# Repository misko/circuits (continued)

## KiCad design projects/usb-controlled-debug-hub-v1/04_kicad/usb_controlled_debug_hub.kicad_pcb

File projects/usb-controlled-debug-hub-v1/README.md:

# USB controlled debug hub v1

Four-port self-powered USB 2.0 debug hub with independent per-port VBUS and
D+/D- control through an onboard USB management function.

Status: commission and exact-part sourcing in progress. No release exists and
the board is not ready to order.

Firmware is outside scope. See `01_docs/BRIEF.md` for the commission and
`01_docs/ARCHITECTURE.md` for the locked topology.

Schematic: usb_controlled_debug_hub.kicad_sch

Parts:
C_AGG_DVDT: 3.3nF; C_0603_1608Metric
C_AGG_IN: 100nF; C_0402_1005Metric
C_AGG_TIMER: 3.3nF; C_0603_1608Metric
C_AND_DATA: 100nF; C_0402_1005Metric
C_AND_PWR: 100nF; C_0402_1005Metric
C_BST: 100nF; C_0402_1005Metric
C_BUCK_IN: 10uF; C_0603_1608Metric
C_BUCK_OUT1, C_BUCK_OUT2: 22uF; C_1210_3225Metric
C_CTRL_VDD: 100nF; C_0402_1005Metric
C_CTRL_VUSB: 330nF; C_0402_1005Metric
C_DATA1, C_DATA2, C_DATA3, C_DATA4: 100nF; C_0402_1005Metric
C_EXP_VDD: 100nF; C_0402_1005Metric
C_HUB_18, C_HUB_18PLL: 1uF; C_0402_1005Metric
C_HUB_A1, C_HUB_A2, C_HUB_A3, C_HUB_A4: 100nF; C_0402_1005Metric
C_HUB_A_BULK: 1uF; C_0402_1005Metric
C_HUB_CR_BULK: 1uF; C_0402_1005Metric
C_HUB_CR_HF: 100nF; C_0402_1005Metric
C_HUB_DD: 100nF; C_0402_1005Metric
C_HUB_PLL: 100nF; C_0402_1005Metric
C_HUB_RESET: 1uF; C_0402_1005Metric
C_PORT1_BULK, C_PORT2_BULK, C_PORT3_BULK, C_PORT4_BULK: 22uF; C_1210_3225Metric
C_PORT1_HF, C_PORT2_HF, C_PORT3_HF, C_PORT4_HF: 100nF; C_0402_1005Metric
C_PWR1_IN, C_PWR2_IN, C_PWR3_IN, C_PWR4_IN: 100nF; C_0402_1005Metric
C_PWR_CTRL_IN: 100nF; C_0402_1005Metric
C_PWR_CTRL_OUT: 1uF; C_0402_1005Metric
C_PWR_CTRL_OUT_HF: 100nF; C_0402_1005Metric
C_TRUNK_BULK: 22uF; C_1210_3225Metric
C_TRUNK_HF: 100nF; C_0402_1005Metric
C_TRUNK_USB: 180uF; CP_Elec_6.3x5.8
C_XTAL1, C_XTAL2: 18pF; C_0402_1005Metric
F_IN: 3568; Fuseholder_Blade_Mini_Keystone_3568
J_PORT1, J_PORT2, J_PORT3, J_PORT4: C503996; KH-AF90DIP-112_Horizontal
J_PWR: C3819953; Phoenix_1935161_PT_1p5_2_5p0_H
J_UP: C86462; USB_B_TE_292304-1_Horizontal
L_MAIN: C15269; Sunlord_SWPA4030S
Q_DATA1, Q_DATA2, Q_DATA3, Q_DATA4: C85047; Diodes_SOT23_2N7002K
R_AGG_ILIM: 1kΩ; R_0603_1608Metric
R_AGG_OV_BOT: 43.2kΩ; R_0603_1608Metric
R_AGG_UV_MID: 10kΩ; R_0603_1608Metric
R_AGG_UV_TOP: 150kΩ; R_0603_1608Metric
R_BOOST0, R_BOOST1: 10kΩ; R_0402_1005Metric
R_CFG0, R_CFG1, R_CFG2: 10kΩ; R_0402_1005Metric
R_CTRL_RESET: 10kΩ; R_0402_1005Metric
R_DATA_CMD1, R_DATA_CMD2, R_DATA_CMD3, R_DATA_CMD4: 10kΩ; R_0402_1005Metric
R_DATA_OE1, R_DATA_OE2, R_DATA_OE3, R_DATA_OE4: 10kΩ; R_0402_1005Metric
R_DATA_OK1, R_DATA_OK2, R_DATA_OK3, R_DATA_OK4: 10kΩ; R_0402_1005Metric
R_DIS6N, R_DIS6P, R_DIS7N, R_DIS7P: 10kΩ; R_0402_1005Metric
R_EXP_RESET: 10kΩ; R_0402_1005Metric
R_GANG: 10kΩ; R_0402_1005Metric
R_HUB_RESET: 10kΩ; R_0402_1005Metric
R_I2C_SCL, R_I2C_SDA: 4.7kΩ; R_0402_1005Metric
R_ILIM1, R_ILIM2, R_ILIM3, R_ILIM4: 165kΩ; R_0402_1005Metric
R_ILIM_CTRL: 165kΩ; R_0402_1005Metric
R_NONREM0, R_NONREM1: 10kΩ; R_0402_1005Metric
R_PWR_CMD1, R_PWR_CMD2, R_PWR_CMD3, R_PWR_CMD4: 10kΩ; R_0402_1005Metric
R_PWR_EN1, R_PWR_EN2, R_PWR_EN3, R_PWR_EN4: 10kΩ; R_0402_1005Metric
R_RBIAS: 12kΩ; R_0402_1005Metric
R_SWAP1, R_SWAP2, R_SWAP3, R_SWAP4, R_SWAP5, R_SWAP6, R_SWAP7: 100kΩ; R_0402_1005Metric
R_VBUS_BOT: 100kΩ; R_0402_1005Metric
R_VBUS_TOP: 100kΩ; R_0402_1005Metric
R_XTAL: 1MΩ; R_0402_1005Metric
U_AGG: C2864845; TI_RPW0010A_VQFN-HR-10_2x2mm_P0.45mm
U_AND_DATA: C6053; TSSOP-14_4.4x5mm_P0.65mm
U_AND_PWR: C6053; TSSOP-14_4.4x5mm_P0.65mm
U_BUCK: C5248536; TSOT-23-6
U_CTRL: C640876; SOIC-14_3.9x8.7mm_P1.27mm
U_DATA1, U_DATA2, U_DATA3, U_DATA4: C11355; MSOP-10_3x3mm_P0.5mm
U_ESD1, U_ESD2, U_ESD3, U_ESD4: C3708426; SOT-23
U_ESD_UP: C3708426; SOT-23
U_EXP: C558584; SSOP-28_5.3x10.2mm_P0.65mm
U_HUB: C478081; QFN-64-1EP_9x9mm_P0.5mm_EP4.7x4.7mm_ThermalVias
U_PWR1, U_PWR2, U_PWR3, U_PWR4: C130056; VSON-8-1EP_3x3mm_P0.65mm_EP1.65x2.4mm_ThermalVias
U_PWR_CTRL: C130056; VSON-8-1EP_3x3mm_P0.65mm_EP1.65x2.4mm_ThermalVias
Y_HUB: C1985204; Crystal_SMD_3225-4Pin_3.2x2.5mm

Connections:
3V3_MAIN: C_AND_DATA.1, C_AND_PWR.1, C_BUCK_OUT1.1, C_BUCK_OUT2.1, C_DATA1.1, C_DATA2.1, C_DATA3.1, C_DATA4.1, C_HUB_A1.1, C_HUB_A2.1, C_HUB_A3.1, C_HUB_A4.1, C_HUB_A_BULK.1, C_HUB_CR_BULK.1, C_HUB_CR_HF.1, C_HUB_DD.1, C_HUB_PLL.1, L_MAIN.2, R_DATA_OE1.1, R_DATA_OE2.1, R_DATA_OE3.1, R_DATA_OE4.1, R_DIS6N.1, R_DIS6P.1, R_DIS7N.1, R_DIS7P.1, R_HUB_RESET.1, R_NONREM0.1, R_SWAP1.2, U_AND_DATA.14 (VCC), U_AND_PWR.14 (VCC), U_BUCK.1 (FB), U_DATA1.1 (VCC), U_DATA2.1 (VCC), U_DATA3.1 (VCC), U_DATA4.1 (VCC), U_HUB.5 (VDDA33_1), U_HUB.10 (VDDA33_2), U_HUB.24 (VDD33CR), U_HUB.46 (VDD33), U_HUB.52 (VDDA33_3), U_HUB.57 (VDDA33_4), U_HUB.64 (VDD33PLL)
AGG_DVDT: C_AGG_DVDT.1, U_AGG.7 (DVDT)
AGG_ILIM: R_AGG_ILIM.1, U_AGG.9 (ILM)
AGG_OV: R_AGG_OV_BOT.1, R_AGG_UV_MID.2, U_AGG.2 (OVLO)
AGG_TIMER: C_AGG_TIMER.1, U_AGG.10 (ITIMER)
AGG_UV: R_AGG_UV_MID.1, R_AGG_UV_TOP.2, U_AGG.1 (EN_UVLO)
BST_3V3: C_BST.1, U_BUCK.6 (BST)
CTRL_RESET_N: R_CTRL_RESET.2, U_CTRL.4 (RST)
CTRL_VUSB_3V3: C_CTRL_VUSB.1, U_CTRL.11 (VUSB)
DATA_CMD1: R_DATA_CMD1.1, U_AND_DATA.2 (1B), U_EXP.25 (GPA4)
DATA_CMD2: R_DATA_CMD2.1, U_AND_DATA.5 (2B), U_EXP.26 (GPA5)
DATA_CMD3: R_DATA_CMD3.1, U_AND_DATA.10 (3B), U_EXP.27 (GPA6)
DATA_CMD4: R_DATA_CMD4.1, U_AND_DATA.13 (4B), U_EXP.28 (GPA7)
DATA_OE1_N: Q_DATA1.3 (D), R_DATA_OE1.2, U_DATA1.10 (OE)
DATA_OE2_N: Q_DATA2.3 (D), R_DATA_OE2.2, U_DATA2.10 (OE)
DATA_OE3_N: Q_DATA3.3 (D), R_DATA_OE3.2, U_DATA3.10 (OE)
DATA_OE4_N: Q_DATA4.3 (D), R_DATA_OE4.2, U_DATA4.10 (OE)
DATA_OK1: Q_DATA1.1 (G), R_DATA_OK1.1, U_AND_DATA.3 (1Y)
DATA_OK2: Q_DATA2.1 (G), R_DATA_OK2.1, U_AND_DATA.6 (2Y)
DATA_OK3: Q_DATA3.1 (G), R_DATA_OK3.1, U_AND_DATA.8 (3Y)
DATA_OK4: Q_DATA4.1 (G), R_DATA_OK4.1, U_AND_DATA.11 (4Y)
EXP_RESET_N: R_EXP_RESET.2, U_EXP.18 (RESET_N)
GND: C_AGG_DVDT.2, C_AGG_IN.2, C_AGG_TIMER.2, C_AND_DATA.2, C_AND_PWR.2, C_BUCK_IN.2, C_BUCK_OUT1.2, C_BUCK_OUT2.2, C_CTRL_VDD.2, C_CTRL_VUSB.2, C_DATA1.2, C_DATA2.2, C_DATA3.2, C_DATA4.2, C_EXP_VDD.2, C_HUB_18.2, C_HUB_18PLL.2, C_HUB_A1.2, C_HUB_A2.2, C_HUB_A3.2, C_HUB_A4.2, C_HUB_A_BULK.2, C_HUB_CR_BULK.2, C_HUB_CR_HF.2, C_HUB_DD.2, C_HUB_PLL.2, C_HUB_RESET.2, C_PORT1_BULK.2, C_PORT1_HF.2, C_PORT2_BULK.2, C_PORT2_HF.2, C_PORT3_BULK.2, C_PORT3_HF.2, C_PORT4_BULK.2, C_PORT4_HF.2, C_PWR1_IN.2, C_PWR2_IN.2, C_PWR3_IN.2, C_PWR4_IN.2, C_PWR_CTRL_IN.2, C_PWR_CTRL_OUT.2, C_PWR_CTRL_OUT_HF.2, C_TRUNK_BULK.2, C_TRUNK_HF.2, C_TRUNK_USB.2, C_XTAL1.2, C_XTAL2.2, J_PORT1.4 (GND), J_PORT1.5 (SHIELD), J_PORT2.4 (GND), J_PORT2.5 (SHIELD), J_PORT3.4 (GND), J_PORT3.5 (SHIELD), J_PORT4.4 (GND), J_PORT4.5 (SHIELD), J_PWR.2 (GND), J_UP.4 (GND), J_UP.5 (SHIELD), Q_DATA1.2 (S), Q_DATA2.2 (S), Q_DATA3.2 (S), Q_DATA4.2 (S), R_AGG_ILIM.2, R_AGG_OV_BOT.2, R_BOOST0.2, R_BOOST1.2, R_CFG0.2, R_CFG1.2, R_CFG2.2, R_DATA_CMD1.2, R_DATA_CMD2.2, R_DATA_CMD3.2, R_DATA_CMD4.2, R_DATA_OK1.2, R_DATA_OK2.2, R_DATA_OK3.2, R_DATA_OK4.2, R_GANG.2, R_ILIM1.2, R_ILIM2.2, R_ILIM3.2, R_ILIM4.2, R_ILIM_CTRL.2, R_NONREM1.2, R_PWR_CMD1.2, R_PWR_CMD2.2, R_PWR_CMD3.2, R_PWR_CMD4.2, R_PWR_EN1.2, R_PWR_EN2.2, R_PWR_EN3.2, R_PWR_EN4.2, R_RBIAS.2, R_SWAP2.2, R_SWAP3.2, R_SWAP4.2, R_SWAP5.2, R_SWAP6.2, R_SWAP7.2, R_VBUS_BOT.2, U_AGG.4 (PGTH), U_AGG.8 (GND), U_AND_DATA.7 (GND), U_AND_PWR.7 (GND), U_BUCK.4 (GND), U_CTRL.14 (VSS), U_DATA1.2 (SEL), U_DATA1.5 (GND), U_DATA2.2 (SEL), U_DATA2.5 (GND), U_DATA3.2 (SEL), U_DATA3.5 (GND), U_DATA4.2 (SEL), U_DATA4.5 (GND), U_ESD1.3 (GND), U_ESD2.3 (GND), U_ESD3.3 (GND), U_ESD4.3 (GND), U_ESD_UP.3 (GND), U_EXP.10 (VSS), U_EXP.15 (A0), U_EXP.16 (A1), U_EXP.17 (A2), U_HUB.65 (EP_VSS), U_PWR1.1 (GND), U_PWR1.9 (EP), U_PWR2.1 (GND), U_PWR2.9 (EP), U_PWR3.1 (GND), U_PWR3.9 (EP), U_PWR4.1 (GND), U_PWR4.9 (EP), U_PWR_CTRL.1 (GND), U_PWR_CTRL.9 (EP), Y_HUB.2 (GND1), Y_HUB.4 (GND2)
HUB_BOOST0: R_BOOST0.1, U_HUB.50 (BOOST0)
HUB_BOOST1: R_BOOST1.1, U_HUB.48 (BOOST1)
HUB_CFG0: R_CFG0.1, U_HUB.41 (CFG_SEL0)
HUB_CFG1: R_CFG1.1, U_HUB.42 (CFG_SEL1)
HUB_CFG2: R_CFG2.1, U_HUB.13 (CFG_SEL2)
HUB_DIS6_N: R_DIS6N.2, U_HUB.53 (DN6_DM)
HUB_DIS6_P: R_DIS6P.2, U_HUB.54 (DN6_DP)
HUB_DIS7_N: R_DIS7N.2, U_HUB.55 (DN7_DM)
HUB_DIS7_P: R_DIS7P.2, U_HUB.56 (DN7_DP)
HUB_GANG: R_GANG.1, U_HUB.34 (GANG_EN)
HUB_NONREM0: R_NONREM0.2, U_HUB.45 (NON_REM0)
HUB_NONREM1: R_NONREM1.1, U_HUB.40 (NON_REM1)
HUB_OCS1_N: U_HUB.28 (OCS1_N), U_PWR_CTRL.8 (FAULT_N)
HUB_OCS2_N: U_HUB.27 (OCS2_N), U_PWR1.8 (FAULT_N)
HUB_OCS3_N: U_HUB.22 (OCS3_N), U_PWR2.8 (FAULT_N)
HUB_OCS4_N: U_HUB.21 (OCS4_N), U_PWR3.8 (FAULT_N)
HUB_OCS5_N: U_HUB.35 (OCS5_N), U_PWR4.8 (FAULT_N)
HUB_PRTPWR1: U_HUB.29 (PRTPWR1), U_PWR_CTRL.4 (EN)
HUB_PRTPWR2: U_AND_PWR.1 (1A), U_HUB.26 (PRTPWR2)
HUB_PRTPWR3: U_AND_PWR.4 (2A), U_HUB.23 (PRTPWR3)
HUB_PRTPWR4: U_AND_PWR.9 (3A), U_HUB.20 (PRTPWR4)
HUB_PRTPWR5: U_AND_PWR.12 (4A), U_HUB.30 (PRTPWR5)
HUB_RESET_N: C_HUB_RESET.1, R_HUB_RESET.2, U_HUB.43 (RESET_N)
HUB_SWAP1: R_SWAP1.1, U_HUB.51 (PRT_SWP1)
HUB_SWAP2: R_SWAP2.1, U_HUB.49 (PRT_SWP2)
HUB_SWAP3: R_SWAP3.1, U_HUB.47 (PRT_SWP3)
HUB_SWAP4: R_SWAP4.1, U_HUB.33 (PRT_SWP4)
HUB_SWAP5: R_SWAP5.1, U_HUB.31 (PRT_SWP5)
HUB_SWAP6: R_SWAP6.1, U_HUB.17 (PRT_SWP6)
HUB_SWAP7: R_SWAP7.1, U_HUB.15 (PRT_SWP7)
HUB_VBUS_SENSE: R_VBUS_BOT.1, R_VBUS_TOP.2, U_HUB.44 (VBUS_DET)
HUB_VDD18: C_HUB_18.1, U_HUB.25 (VDD18)
HUB_VDD18PLL: C_HUB_18PLL.1, U_HUB.62 (VDD18PLL)
I2C_SCL: R_I2C_SCL.2, U_CTRL.10 (SCL), U_EXP.12 (SCL)
I2C_SDA: R_I2C_SDA.2, U_CTRL.9 (SDA), U_EXP.13 (SDA)
ILIM1: R_ILIM1.1, U_PWR1.5 (ILIM)
ILIM2: R_ILIM2.1, U_PWR2.5 (ILIM)
ILIM3: R_ILIM3.1, U_PWR3.5 (ILIM)
ILIM4: R_ILIM4.1, U_PWR4.5 (ILIM)
ILIM_CTRL: R_ILIM_CTRL.1, U_PWR_CTRL.5 (ILIM)
MGMT_N: U_CTRL.12 (D_MINUS), U_HUB.2 (DN1_DP)
MGMT_P: U_CTRL.13 (D_PLUS), U_HUB.1 (DN1_DM)
P1_HUB_N: U_DATA1.3 (D_PLUS), U_HUB.3 (DN2_DM)
P1_HUB_P: U_DATA1.4 (D_MINUS), U_HUB.4 (DN2_DP)
P1_PORT_N: J_PORT1.2 (D_MINUS), U_DATA1.7 (HSD1_PLUS), U_ESD1.2 (IO2)
P1_PORT_P: J_PORT1.3 (D_PLUS), U_DATA1.6 (HSD1_MINUS), U_ESD1.1 (IO1)
P2_HUB_N: U_DATA2.3 (D_PLUS), U_HUB.6 (DN3_DM)
P2_HUB_P: U_DATA2.4 (D_MINUS), U_HUB.7 (DN3_DP)
P2_PORT_N: J_PORT2.2 (D_MINUS), U_DATA2.7 (HSD1_PLUS), U_ESD2.2 (IO2)
P2_PORT_P: J_PORT2.3 (D_PLUS), U_DATA2.6 (HSD1_MINUS), U_ESD2.1 (IO1)
P3_HUB_N: U_DATA3.3 (D_PLUS), U_HUB.8 (DN4_DM)
P3_HUB_P: U_DATA3.4 (D_MINUS), U_HUB.9 (DN4_DP)
P3_PORT_N: J_PORT3.2 (D_MINUS), U_DATA3.7 (HSD1_PLUS), U_ESD3.2 (IO2)
P3_PORT_P: J_PORT3.3 (D_PLUS), U_DATA3.6 (HSD1_MINUS), U_ESD3.1 (IO1)
P4_HUB_N: U_DATA4.3 (D_PLUS), U_HUB.11 (DN5_DM)
P4_HUB_P: U_DATA4.4 (D_MINUS), U_HUB.12 (DN5_DP)
P4_PORT_N: J_PORT4.2 (D_MINUS), U_DATA4.7 (HSD1_PLUS), U_ESD4.2 (IO2)
P4_PORT_P: J_PORT4.3 (D_PLUS), U_DATA4.6 (HSD1_MINUS), U_ESD4.1 (IO1)
P5V_FUSED: C_AGG_IN.1, F_IN.2 (FUSE_OUT), R_AGG_UV_TOP.1, U_AGG.5 (IN)
P5V_PROTECTED: C_BUCK_IN.1, C_PWR1_IN.1, C_PWR2_IN.1, C_PWR3_IN.1, C_PWR4_IN.1, C_PWR_CTRL_IN.1, C_TRUNK_BULK.1, C_TRUNK_HF.1, C_TRUNK_USB.1, U_AGG.6 (OUT), U_BUCK.2 (EN), U_BUCK.3 (VIN), U_PWR1.2 (IN1), U_PWR1.3 (IN2), U_PWR2.2 (IN1), U_PWR2.3 (IN2), U_PWR3.2 (IN1), U_PWR3.3 (IN2), U_PWR4.2 (IN1), U_PWR4.3 (IN2), U_PWR_CTRL.2 (IN1), U_PWR_CTRL.3 (IN2)
P5V_RAW: F_IN.1 (FUSE_IN), J_PWR.1 (P5V_RAW)
PWR_CMD1: R_PWR_CMD1.1, U_AND_PWR.2 (1B), U_EXP.21 (GPA0)
PWR_CMD2: R_PWR_CMD2.1, U_AND_PWR.5 (2B), U_EXP.22 (GPA1)
PWR_CMD3: R_PWR_CMD3.1, U_AND_PWR.10 (3B), U_EXP.23 (GPA2)
PWR_CMD4: R_PWR_CMD4.1, U_AND_PWR.13 (4B), U_EXP.24 (GPA3)
PWR_EN1: R_PWR_EN1.1, U_AND_DATA.1 (1A), U_AND_PWR.3 (1Y), U_PWR1.4 (EN)
PWR_EN2: R_PWR_EN2.1, U_AND_DATA.4 (2A), U_AND_PWR.6 (2Y), U_PWR2.4 (EN)
PWR_EN3: R_PWR_EN3.1, U_AND_DATA.9 (3A), U_AND_PWR.8 (3Y), U_PWR3.4 (EN)
PWR_EN4: R_PWR_EN4.1, U_AND_DATA.12 (4A), U_AND_PWR.11 (4Y), U_PWR4.4 (EN)
RBIAS: R_RBIAS.1, U_HUB.63 (RBIAS)
SW_3V3: C_BST.2, L_MAIN.1, U_BUCK.5 (SW)
UP_HUB_N: J_UP.2 (D_MINUS), U_ESD_UP.1 (IO1), U_HUB.58 (UP_DM)
UP_HUB_P: J_UP.3 (D_PLUS), U_ESD_UP.2 (IO2), U_HUB.59 (UP_DP)
USB_UP_VBUS: J_UP.1 (VBUS), R_VBUS_TOP.1
VBUS1_SW: C_PORT1_BULK.1, C_PORT1_HF.1, J_PORT1.1 (VBUS), U_PWR1.6 (OUT1), U_PWR1.7 (OUT2)
VBUS2_SW: C_PORT2_BULK.1, C_PORT2_HF.1, J_PORT2.1 (VBUS), U_PWR2.6 (OUT1), U_PWR2.7 (OUT2)
VBUS3_SW: C_PORT3_BULK.1, C_PORT3_HF.1, J_PORT3.1 (VBUS), U_PWR3.6 (OUT1), U_PWR3.7 (OUT2)
VBUS4_SW: C_PORT4_BULK.1, C_PORT4_HF.1, J_PORT4.1 (VBUS), U_PWR4.6 (OUT1), U_PWR4.7 (OUT2)
VBUS_CTRL: C_CTRL_VDD.1, C_EXP_VDD.1, C_PWR_CTRL_OUT.1, C_PWR_CTRL_OUT_HF.1, R_CTRL_RESET.1, R_EXP_RESET.1, R_I2C_SCL.1, R_I2C_SDA.1, U_CTRL.1 (VDD), U_EXP.9 (VDD), U_PWR_CTRL.6 (OUT1), U_PWR_CTRL.7 (OUT2)
XTAL1: C_XTAL1.1, R_XTAL.1, U_HUB.61 (XTAL1), Y_HUB.1 (X1)
XTAL2: C_XTAL2.1, R_XTAL.2, U_HUB.60 (XTAL2), Y_HUB.3 (X2)

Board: 4 copper layers, 146 parts (9 on the bottom side), 104 nets, no tracks yet.

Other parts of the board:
FID1, FID2, FID3: Fiducial_1mm_Mask2mm
H1, H2, H3, H4: MountingHole_3.2mm_M3

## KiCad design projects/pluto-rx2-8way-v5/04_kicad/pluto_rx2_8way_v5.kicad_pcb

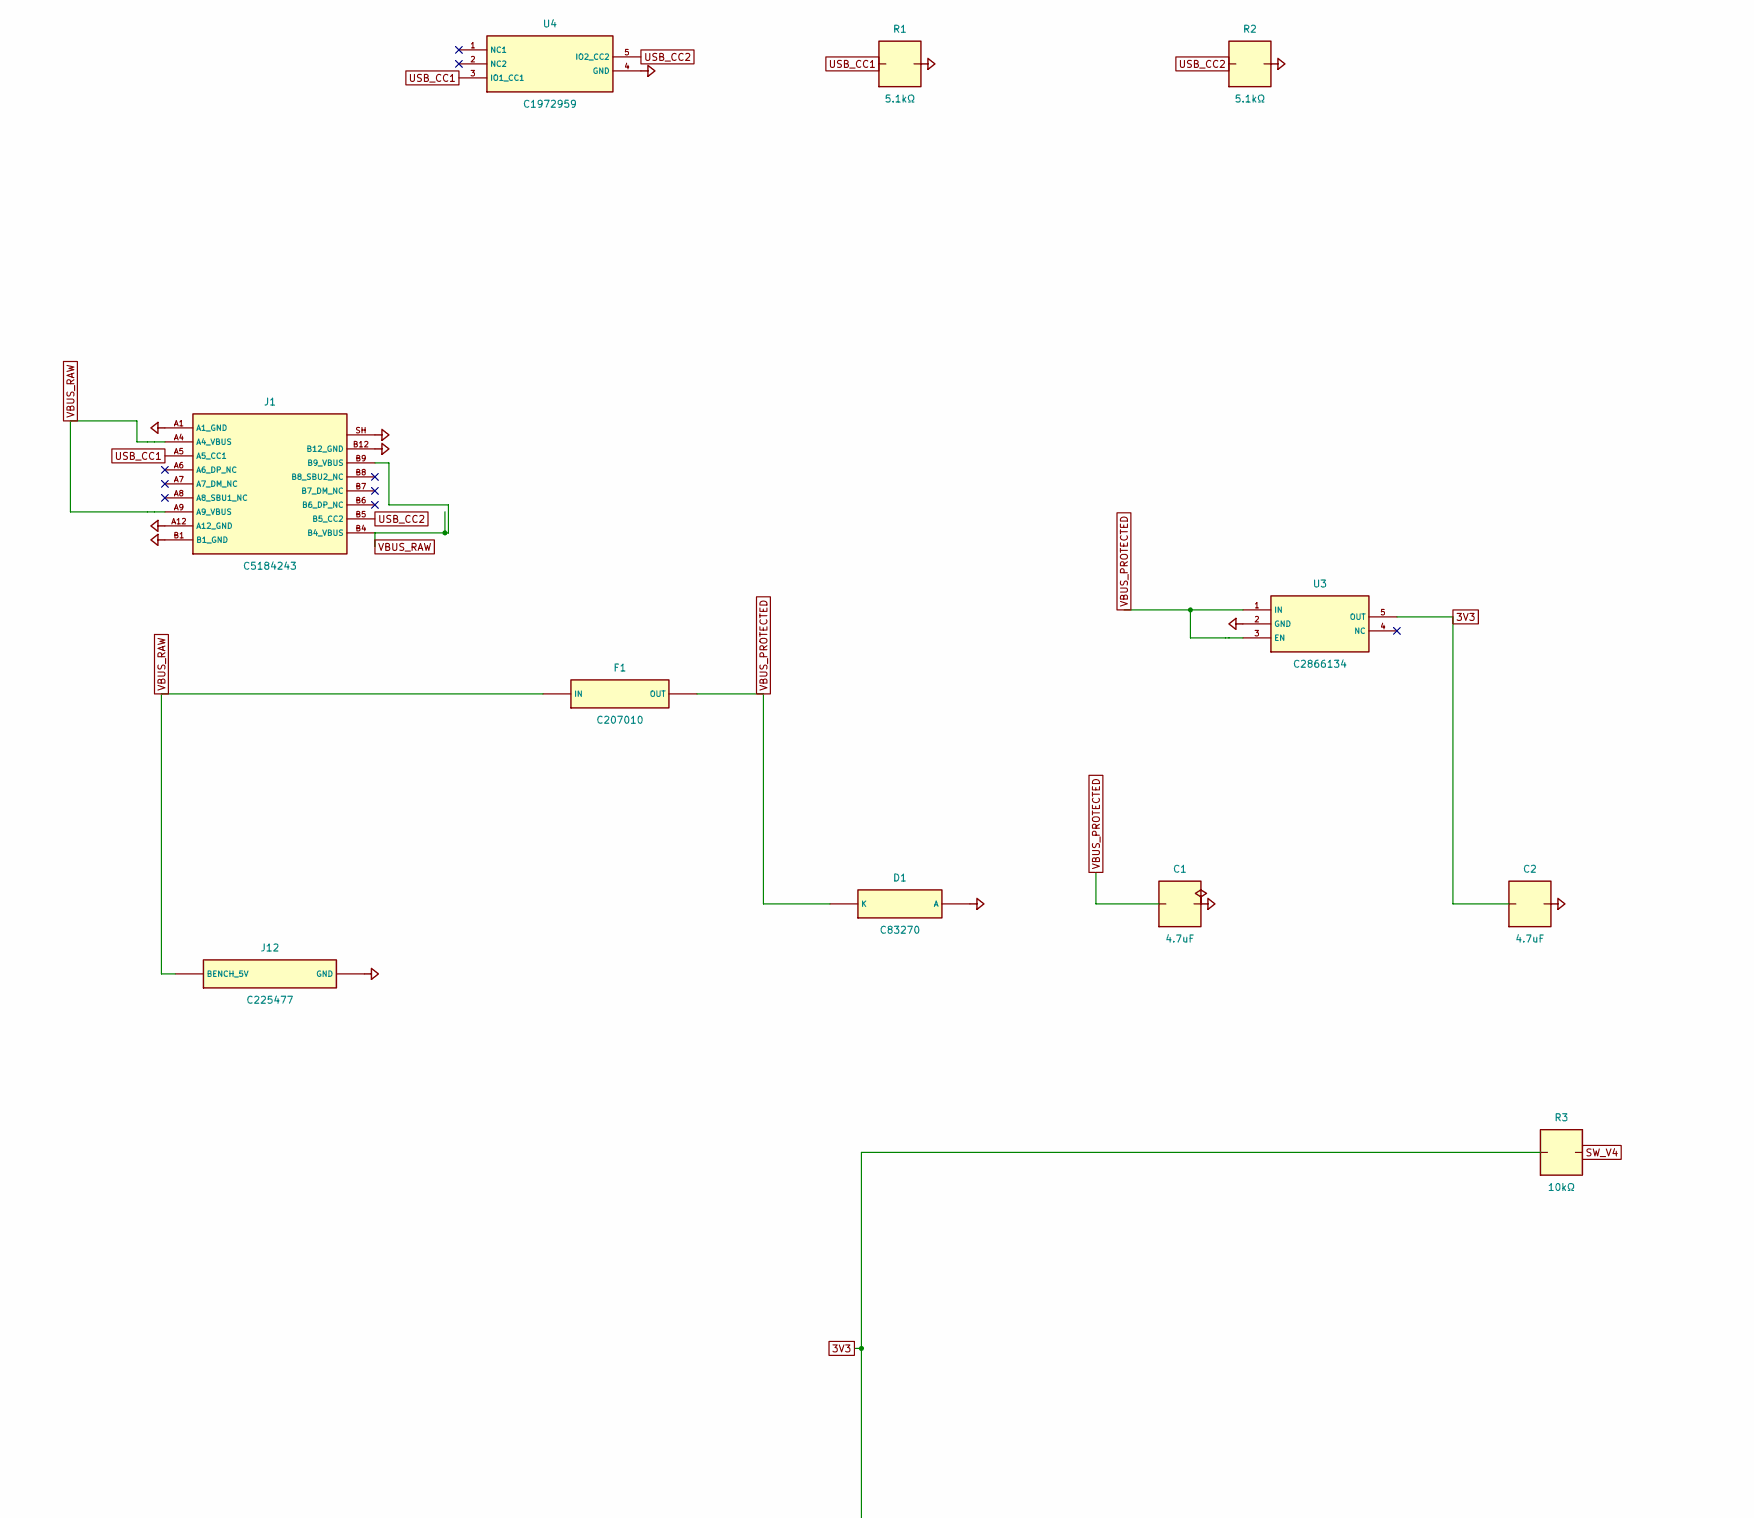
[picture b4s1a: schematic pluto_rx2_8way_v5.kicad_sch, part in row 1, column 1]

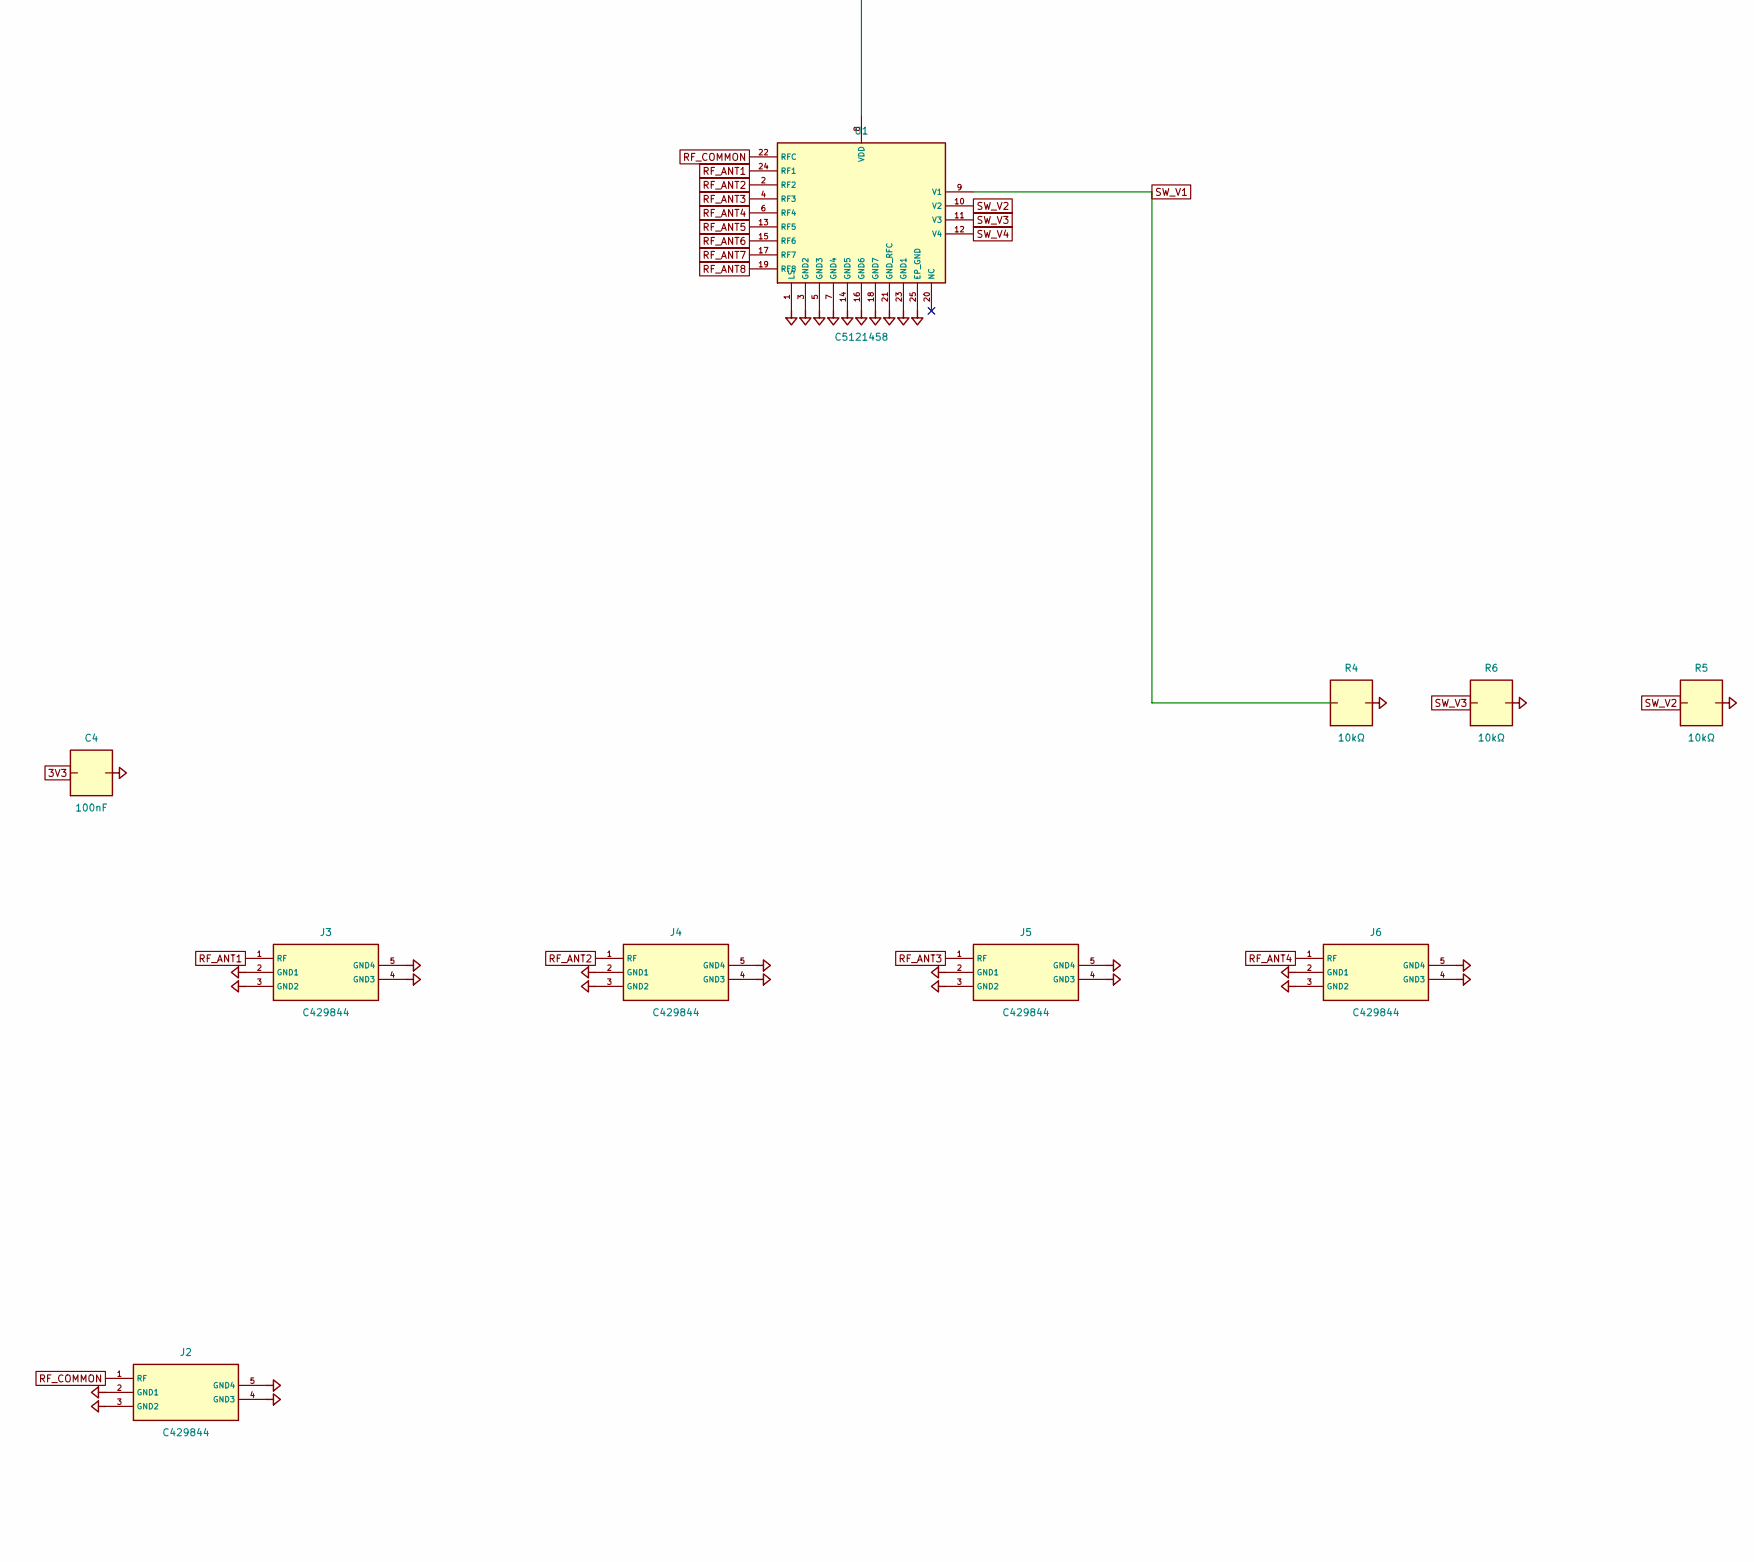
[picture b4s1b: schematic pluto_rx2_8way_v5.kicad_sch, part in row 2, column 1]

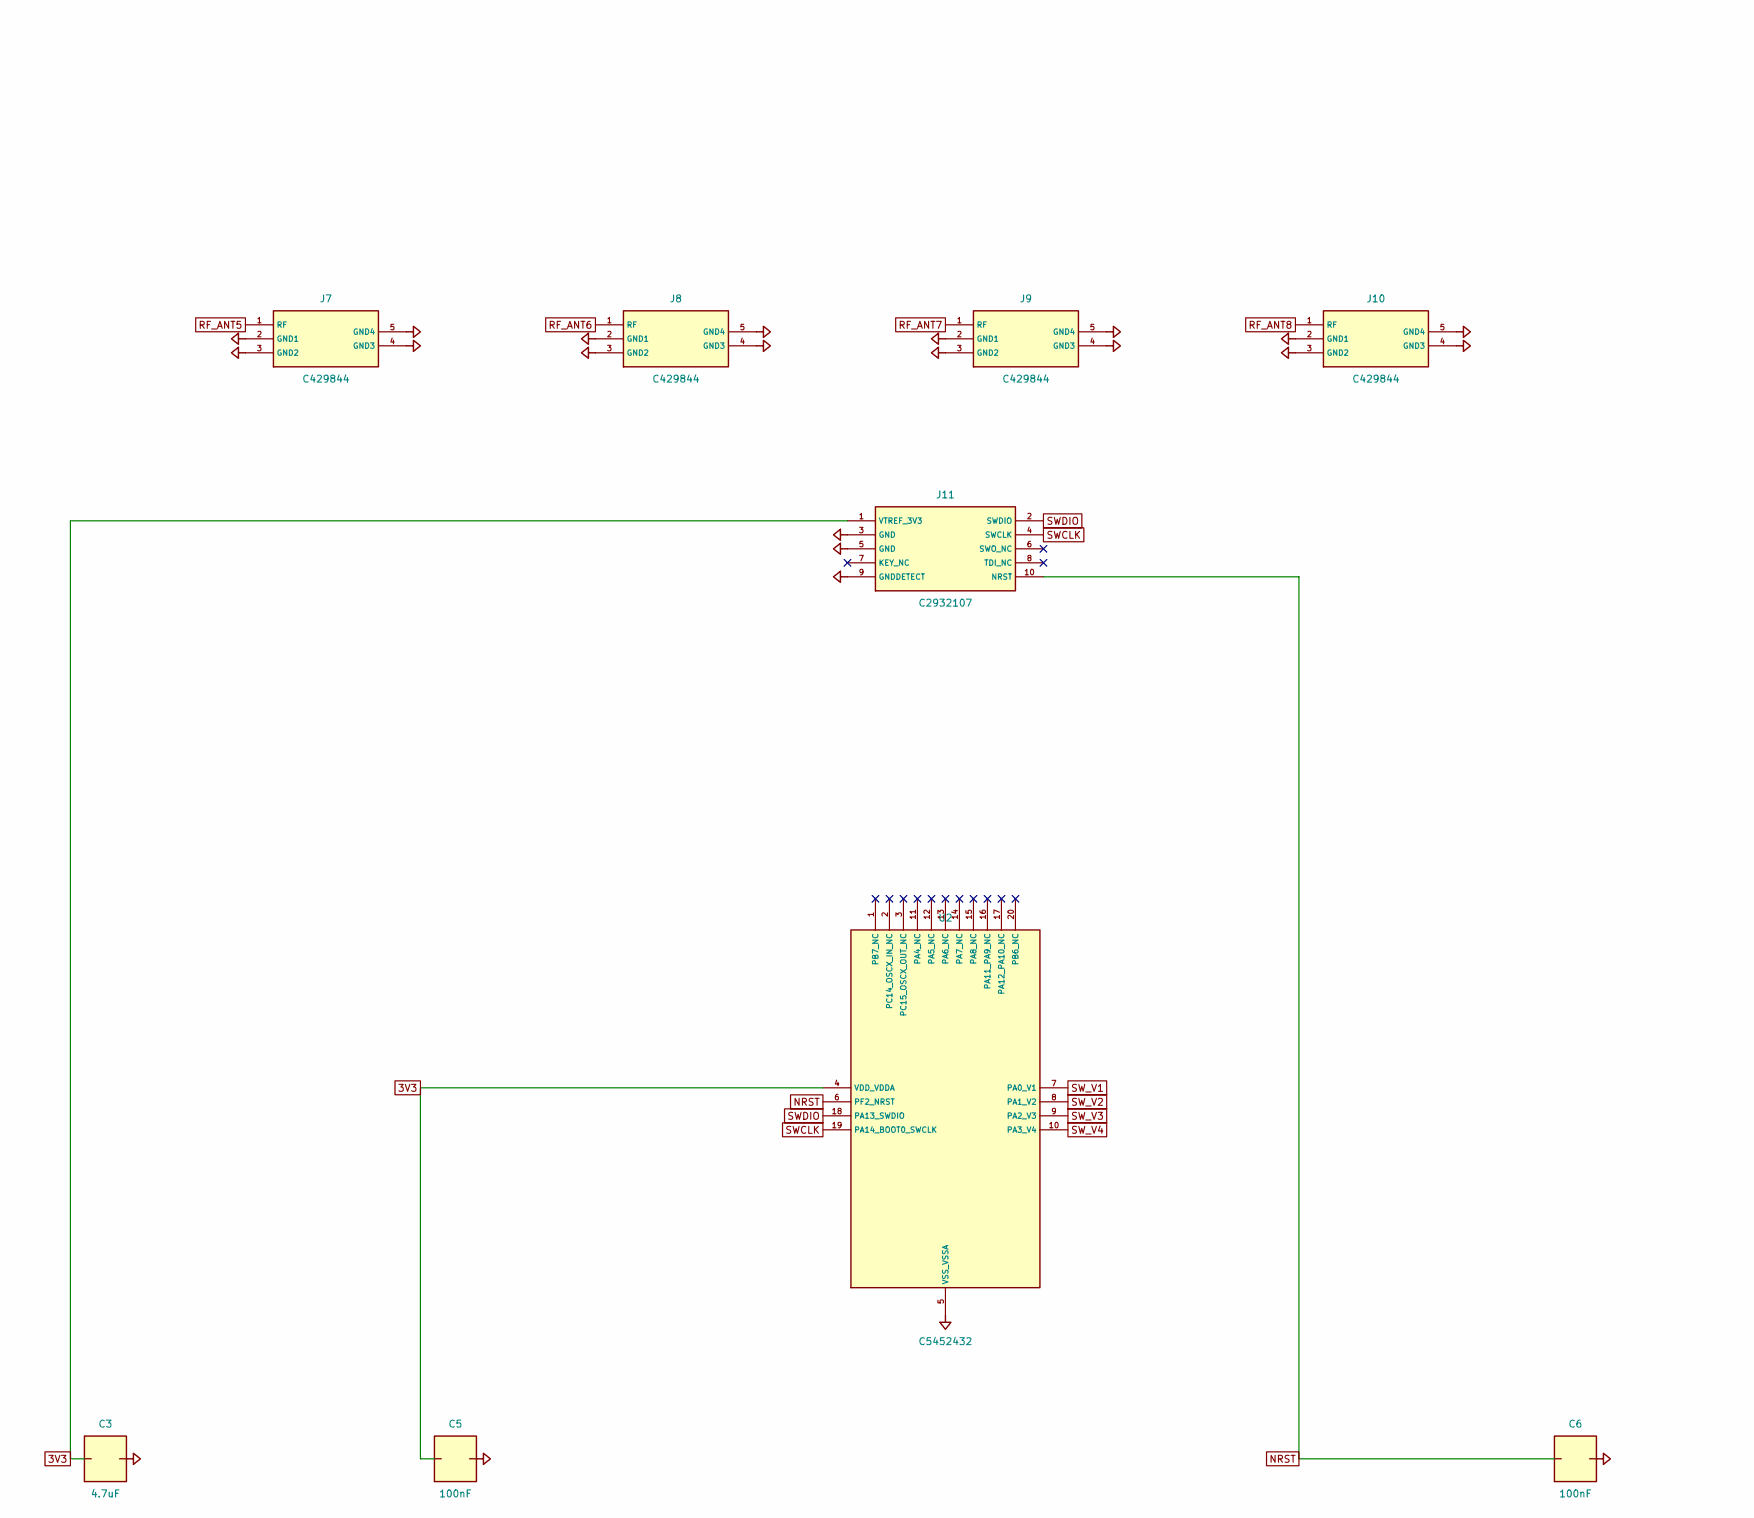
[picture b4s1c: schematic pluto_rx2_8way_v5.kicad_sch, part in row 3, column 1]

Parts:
C1, C2, C3: 4.7uF; C_0603_1608Metric
C4, C5, C6: 100nF; C_0402_1005Metric
D1: C83270; D_SMB
F1: C207010; Fuse_0603_1608Metric
J1: C5184243; GCT_USB4105_GF_A_120
J2, J3, J4, J5, J6, J7, J8, J9, J10: C429844; Amphenol_901_143_6RFX
J11: C2932107; Samtec_FTSH_105_01_L_DV_K_P_TR
J12: C225477; PinHeader_1x02_P2.54mm_Vertical
R1, R2: 5.1kΩ; R_0402_1005Metric
R3, R4, R5, R6: 10kΩ; R_0402_1005Metric
U1: C5121458; Psemi_PE42482_QFN24_4x4_P0.5
U2: C5452432; TSSOP-20_4.4x6.5mm_P0.65mm
U3: C2866134; SOT-23-5
U4: C1972959; SOT-553

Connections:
3V3: C2.1, C3.1, C4.1, C5.1, J11.1 (VTREF_3V3), R3.1, U1.8 (VDD), U2.4 (VDD_VDDA), U3.5 (OUT)
GND: C1.2, C2.2, C3.2, C4.2, C5.2, C6.2, D1.2 (A), J1.A1 (A1_GND), J1.A12 (A12_GND), J1.B1 (B1_GND), J1.B12 (B12_GND), J1.SH, J2.2 (GND1), J2.3 (GND2), J2.4 (GND3), J2.5 (GND4), J3.2 (GND1), J3.3 (GND2), J3.4 (GND3), J3.5 (GND4), J4.2 (GND1), J4.3 (GND2), J4.4 (GND3), J4.5 (GND4), J5.2 (GND1), J5.3 (GND2), J5.4 (GND3), J5.5 (GND4), J6.2 (GND1), J6.3 (GND2), J6.4 (GND3), J6.5 (GND4), J7.2 (GND1), J7.3 (GND2), J7.4 (GND3), J7.5 (GND4), J8.2 (GND1), J8.3 (GND2), J8.4 (GND3), J8.5 (GND4), J9.2 (GND1), J9.3 (GND2), J9.4 (GND3), J9.5 (GND4), J10.2 (GND1), J10.3 (GND2), J10.4 (GND3), J10.5 (GND4), J11.3 (GND), J11.5 (GND), J11.9 (GNDDETECT), J12.2 (GND), R1.2, R2.2, R4.2, R5.2, R6.2, U1.1 (LS), U1.3 (GND2), U1.5 (GND3), U1.7 (GND4), U1.14 (GND5), U1.16 (GND6), U1.18 (GND7), U1.21 (GND_RFC), U1.23 (GND1), U1.25 (EP_GND), U2.5 (VSS_VSSA), U3.2 (GND), U4.4 (GND)
NRST: C6.1, J11.10 (NRST), U2.6 (PF2_NRST)
RF_ANT1: J3.1 (RF), U1.24 (RF1)
RF_ANT2: J4.1 (RF), U1.2 (RF2)
RF_ANT3: J5.1 (RF), U1.4 (RF3)
RF_ANT4: J6.1 (RF), U1.6 (RF4)
RF_ANT5: J7.1 (RF), U1.13 (RF5)
RF_ANT6: J8.1 (RF), U1.15 (RF6)
RF_ANT7: J9.1 (RF), U1.17 (RF7)
RF_ANT8: J10.1 (RF), U1.19 (RF8)
RF_COMMON: J2.1 (RF), U1.22 (RFC)
SWCLK: J11.4 (SWCLK), U2.19 (PA14_BOOT0_SWCLK)
SWDIO: J11.2 (SWDIO), U2.18 (PA13_SWDIO)
SW_V1: R4.1, U1.9 (V1), U2.7 (PA0_V1)
SW_V2: R5.1, U1.10 (V2), U2.8 (PA1_V2)
SW_V3: R6.1, U1.11 (V3), U2.9 (PA2_V3)
SW_V4: R3.2, U1.12 (V4), U2.10 (PA3_V4)
USB_CC1: J1.A5 (A5_CC1), R1.1, U4.3 (IO1_CC1)
USB_CC2: J1.B5 (B5_CC2), R2.1, U4.5 (IO2_CC2)
VBUS_PROTECTED: C1.1, D1.1 (K), F1.2 (OUT), U3.1 (IN), U3.3 (EN)
VBUS_RAW: F1.1 (IN), J1.A4 (A4_VBUS), J1.A9 (A9_VBUS), J1.B4 (B4_VBUS), J1.B9 (B9_VBUS), J12.1 (BENCH_5V)

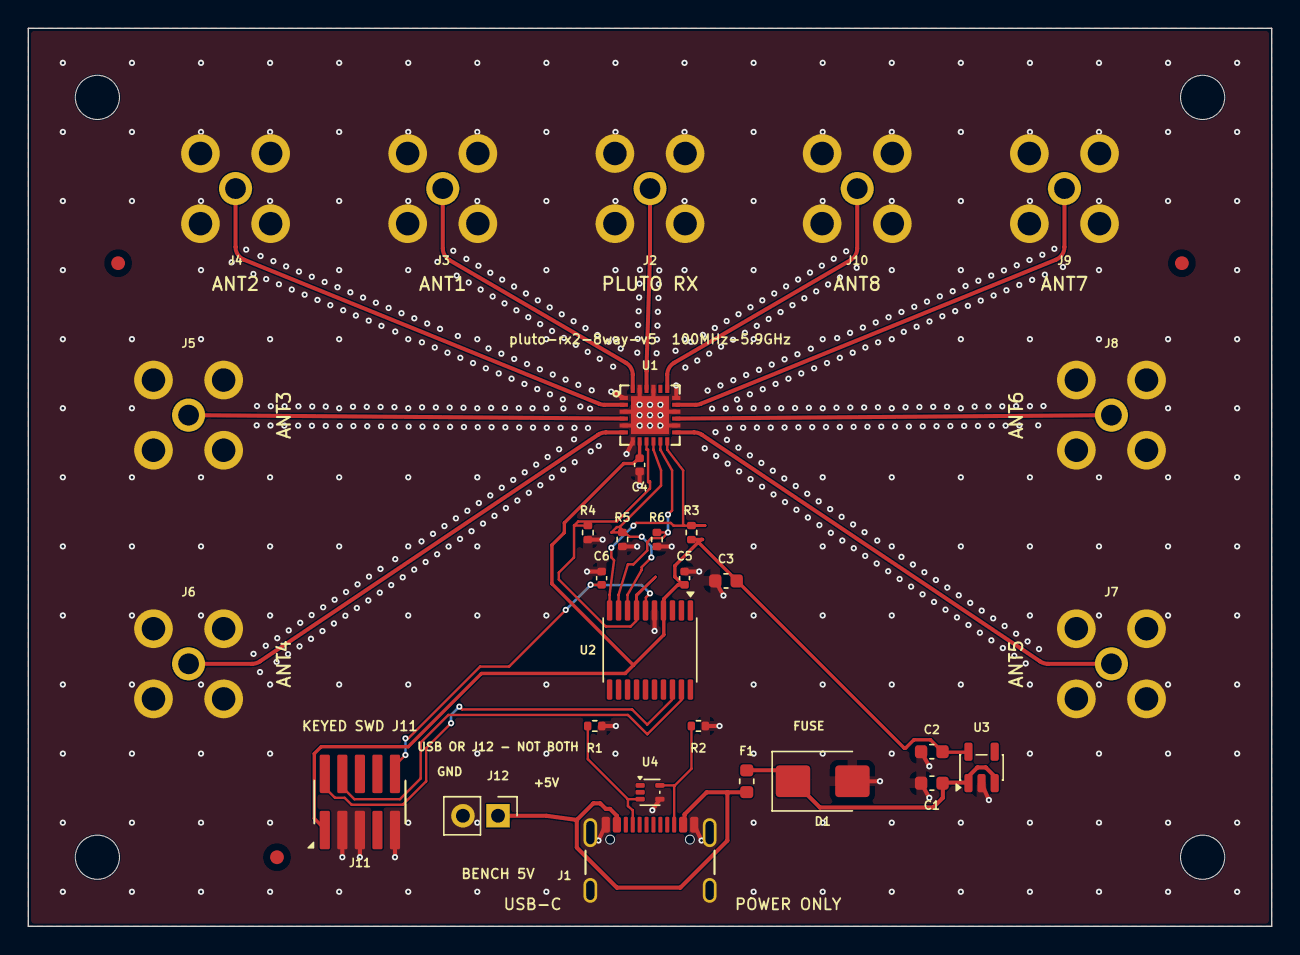
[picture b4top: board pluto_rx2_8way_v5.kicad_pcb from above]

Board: 4 copper layers, 90.0 x 65.0 mm, 37 parts (0 on the bottom side), 22 nets.

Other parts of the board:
FID1, FID2, FID3: Fiducial_1mm_Mask2mm
H1, H2, H3, H4: MountingHole_3.2mm_M3

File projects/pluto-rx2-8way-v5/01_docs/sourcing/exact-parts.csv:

Comment,Designator,Footprint,LCSC
PE42482A-X,U1,Package_DFN_QFN:QFN-24-1EP_4x4mm_P0.5mm,C5121458
STM32C011F4P6,U2,Package_SO:TSSOP-20_4.4x6.5mm_P0.65mm,C5452432
TPS7A2433DBVR,U3,Package_TO_SOT_SMD:SOT-23-5,C2866134
TPD2E2U06DRLR,U4,Package_TO_SOT_SMD:SOT-553,C1972959
USB4105-GF-A-120,J1,pluto_rx2_8way_v5:GCT_USB4105_GF_A_120,C5184243
FTSH-105-01-L-DV-K-P-TR,J11,pluto_rx2_8way_v5:Samtec_FTSH_105_01_L_DV_K_P_TR,C2932107
901-143-6RFX,"J2,J3,J4,J5,J6,J7,J8,J9,J10",pluto_rx2_8way_v5:Amphenol_901_143_6RFX,C429844
0603L010YR,F1,Fuse:Fuse_0603_1608Metric,C207010
SMBJ6.0A,D1,Diode_SMD:D_SMB,C83270
5.1k,"R1,R2",Resistor_SMD:R_0402_1005Metric,C105872
10k,"R3,R4,R5,R6",Resistor_SMD:R_0402_1005Metric,C60490
4.7uF 16V,"C1,C2,C3",Capacitor_SMD:C_0603_1608Metric,C19666
100nF,"C4,C5,C6",Capacitor_SMD:C_0402_1005Metric,C1525
